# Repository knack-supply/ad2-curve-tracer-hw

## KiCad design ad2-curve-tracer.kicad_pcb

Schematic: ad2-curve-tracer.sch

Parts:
C1: 0.1u; C_0603_1608Metric_Pad0.84x1.00mm_HandSolder; MPN CL10B154KA8SFNC
J1: Conn_02x15_Odd_Even; PinSocket_2x15_P2.54mm_Horizontal; MPN PPPC152LJBN-RC
J2: Conn_02x07_Counter_Clockwise; DIP-14_W7.62mm_Socket_LongPads; MPN 214-3339-00-0602J
J3: Conn_01x08; TO-5-8; MPN 917-43-108-41-005000
Q1: BC846BPDW1; SOT-363_SC-70-6_Handsoldering; MPN BC847BPDW1T3G
R1: 100k; R_0603_1608Metric_Pad0.84x1.00mm_HandSolder; MPN RC0603JR-07100KL
R2, R3: 1; R_0603_1608Metric_Pad0.84x1.00mm_HandSolder; MPN RC0603FR-071RL
R4: 100; R_0603_1608Metric_Pad0.84x1.00mm_HandSolder; MPN RC0603FR-07100RL
U1: LMC7101; SOT-23-5_HandSoldering; MPN LMC7101BIM5/NOPB

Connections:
+5V: C1.2, J1.23, Q1.6 (C1), U1.2
An: J1.27, J1.30, J2.1, J2.4, J2.7, J2.14, J3.4, J3.7, R4.2
B|G: J2.2, J2.5, J3.3, J3.8, R1.1
Ca: J1.19, J1.20, J1.25, J1.26, J1.28, J2.3, J2.6, J2.8, J2.9, J2.10, J2.11, J2.12, J2.13, J3.1, J3.2, J3.5, J3.6
unnamed: Q1.1 (E1), R2.1
unnamed: Q1.2 (B1), Q1.5 (B2), U1.1
unnamed: Q1.3 (C2), R3.2
VEE: C1.1, J1.24, Q1.4 (E2), U1.5
testBaseBias: J1.22, R1.2
testV: J1.29, R2.2, R3.1, R4.1, U1.4
testVset: J1.21, U1.3

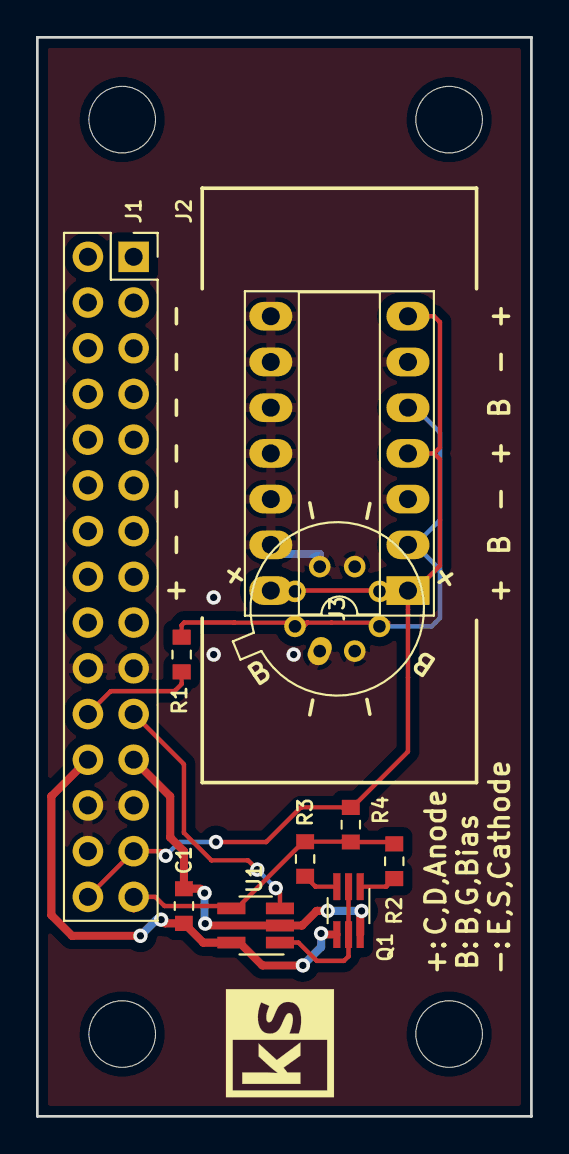
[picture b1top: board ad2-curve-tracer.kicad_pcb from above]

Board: 2 copper layers, 27.4 x 59.9 mm, 10 parts (0 on the bottom side), 11 nets.

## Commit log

2018-05-10 initial version
